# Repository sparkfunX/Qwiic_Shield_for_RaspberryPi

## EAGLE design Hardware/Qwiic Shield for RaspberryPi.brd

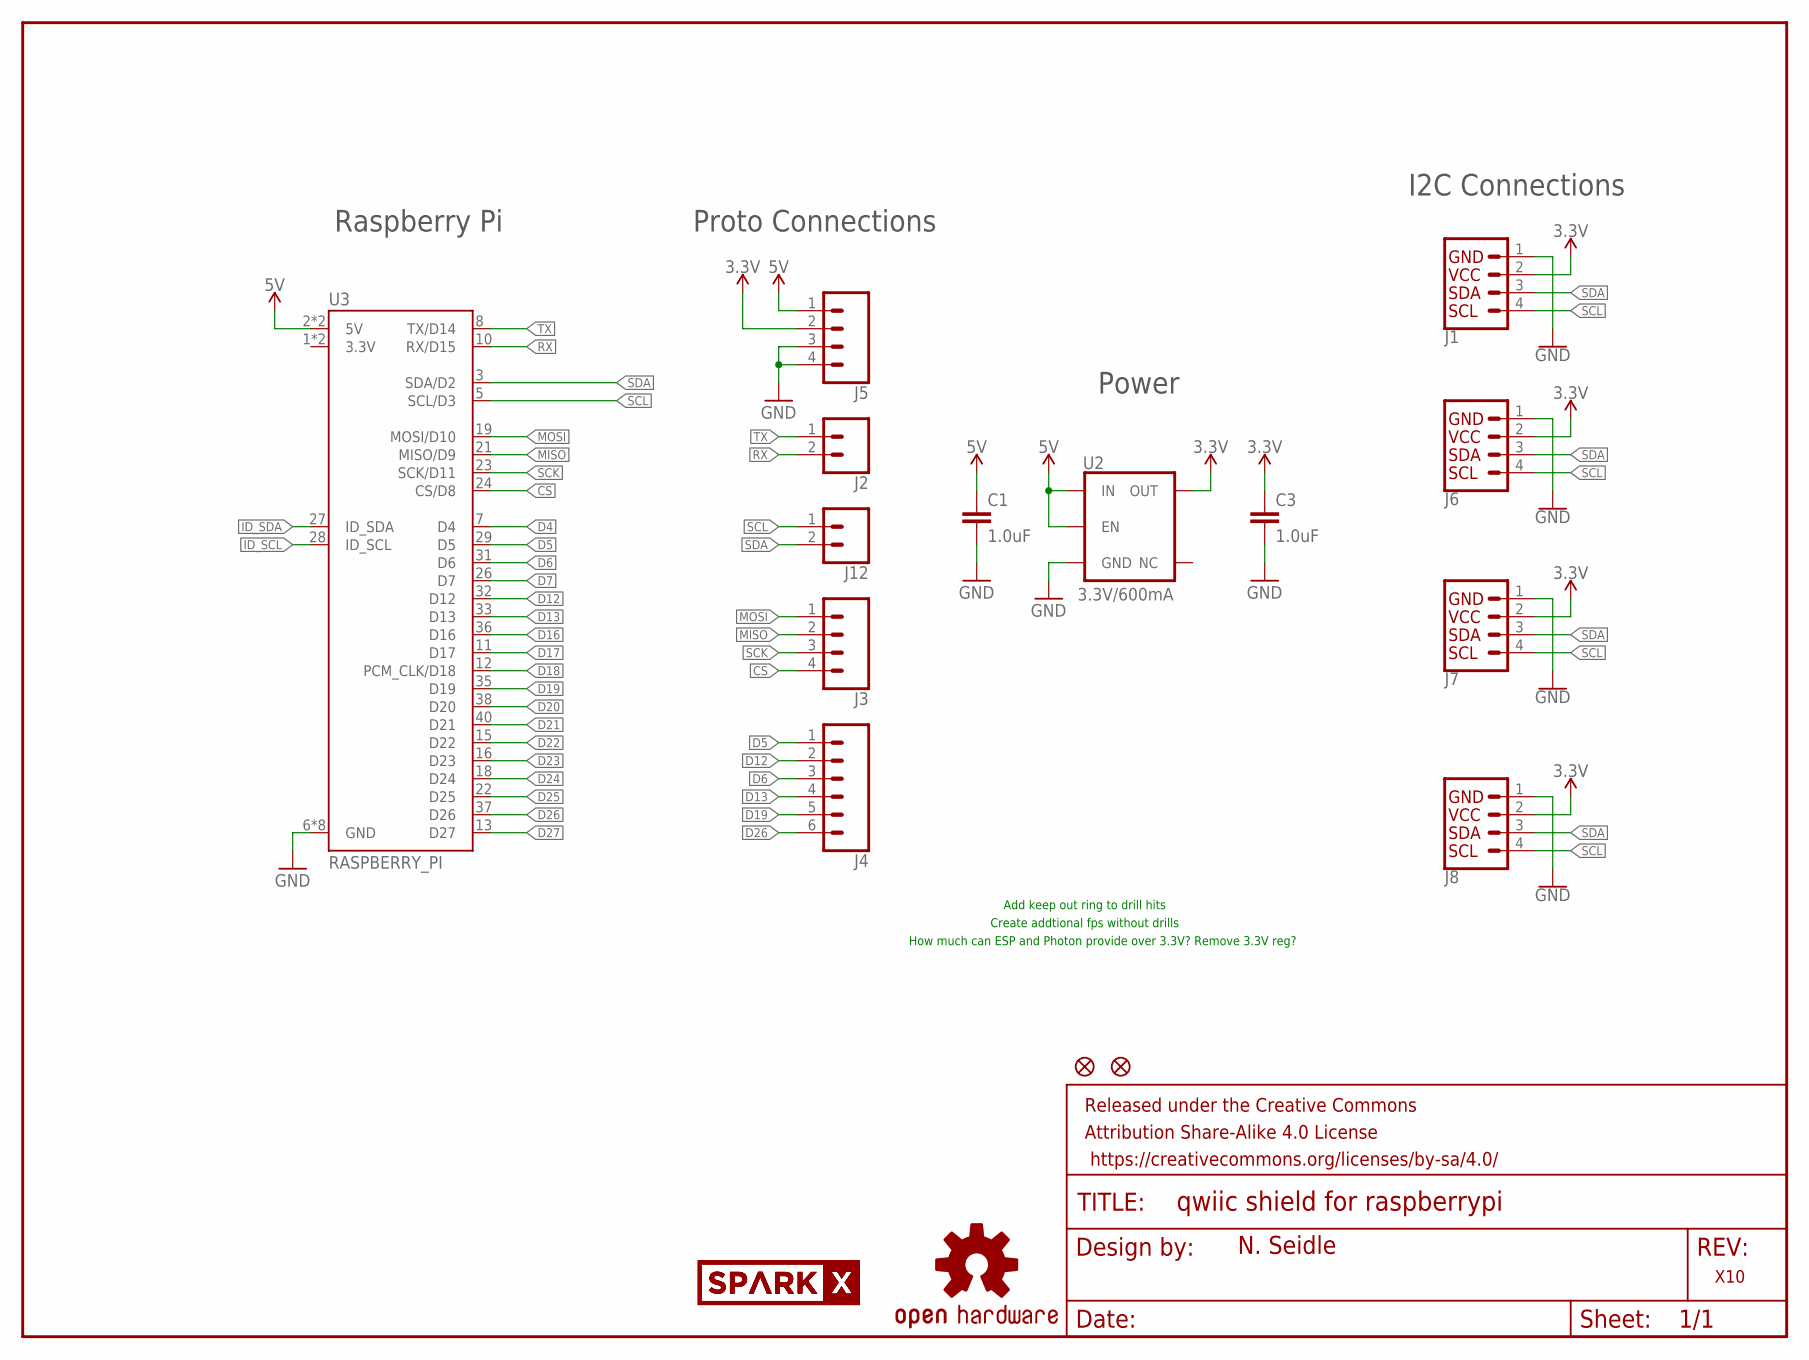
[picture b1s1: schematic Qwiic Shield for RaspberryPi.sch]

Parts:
C1, C3: 1.0uF; 0603
FD1, FD2: FIDUCIAL1X2; FIDUCIAL-1X2
FRAME1: FRAME-LETTER; CREATIVE_COMMONS
J1, J6, J7, J8: I2C_STANDARDJS-1MM; 1X04_1MM_RA
J2, J12: CONN_021X02_NO_SILK; 1X02_NO_SILK
J3, J5: CONN_041X04_NO_SILK; 1X04_NO_SILK
J4: CONN_06NO_SILK_FEMALE_PTH; 1X06_NO_SILK
LOGO1: OSHW-LOGOMINI; OSHW-LOGO-MINI
U2: 3.3V/600mA; SOT23-5
U3: RASPBERRY_PI; RASPBERRY_PI_SHIELD_HOLES
U$1: SPARKX-LOGO3; SPARKX-SMALL
U$2: SPARKX-LOGO5; SPARKX-LARGE

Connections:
3.3V: C3.1, J1.2 (VCC), J5.2, J6.2 (VCC), J7.2 (VCC), J8.2 (VCC), U2.5 (OUT)
5V: C1.1, J5.1, U2.1 (IN), U2.3 (EN), U3.2 (5V), U3.4 (5V)
CS: J3.4, U3.24 (CS/D8)
D4: U3.7 (D4)
D5: J4.1, U3.29 (D5)
D6: J4.3, U3.31 (D6)
D7: U3.26 (D7)
D12: J4.2, U3.32 (D12)
D13: J4.4, U3.33 (D13)
D16: U3.36 (D16)
D17: U3.11 (D17)
D18: U3.12 (PCM_CLK/D18)
D19: J4.5, U3.35 (D19)
D20: U3.38 (D20)
D21: U3.40 (D21)
D22: U3.15 (D22)
D23: U3.16 (D23)
D24: U3.18 (D24)
D25: U3.22 (D25)
D26: J4.6, U3.37 (D26)
D27: U3.13 (D27)
GND: C1.2, C3.2, J1.1 (GND), J5.3, J5.4, J6.1 (GND), J7.1 (GND), J8.1 (GND), U2.2 (GND), U3.6 (GND), U3.9 (GND), U3.14 (GND), U3.20 (GND), U3.25 (GND), U3.30 (GND), U3.34 (GND), U3.39 (GND)
ID_SCL: U3.28 (ID_SCL)
ID_SDA: U3.27 (ID_SDA)
MISO: J3.2, U3.21 (MISO/D9)
MOSI: J3.1, U3.19 (MOSI/D10)
RX: J2.2, U3.10 (RX/D15)
SCK: J3.3, U3.23 (SCK/D11)
SCL: J1.4 (SCL), J6.4 (SCL), J7.4 (SCL), J8.4 (SCL), J12.1, U3.5 (SCL/D3)
SDA: J1.3 (SDA), J6.3 (SDA), J7.3 (SDA), J8.3 (SDA), J12.2, U3.3 (SDA/D2)
TX: J2.1, U3.8 (TX/D14)

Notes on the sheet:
N. Seidle
Raspberry Pi
X10
I2C Connections
Proto Connections
Power
How much can ESP and Photon provide over 3.3V? Remove 3.3V reg?
Create addtional fps without drills
Add keep out ring to drill hits

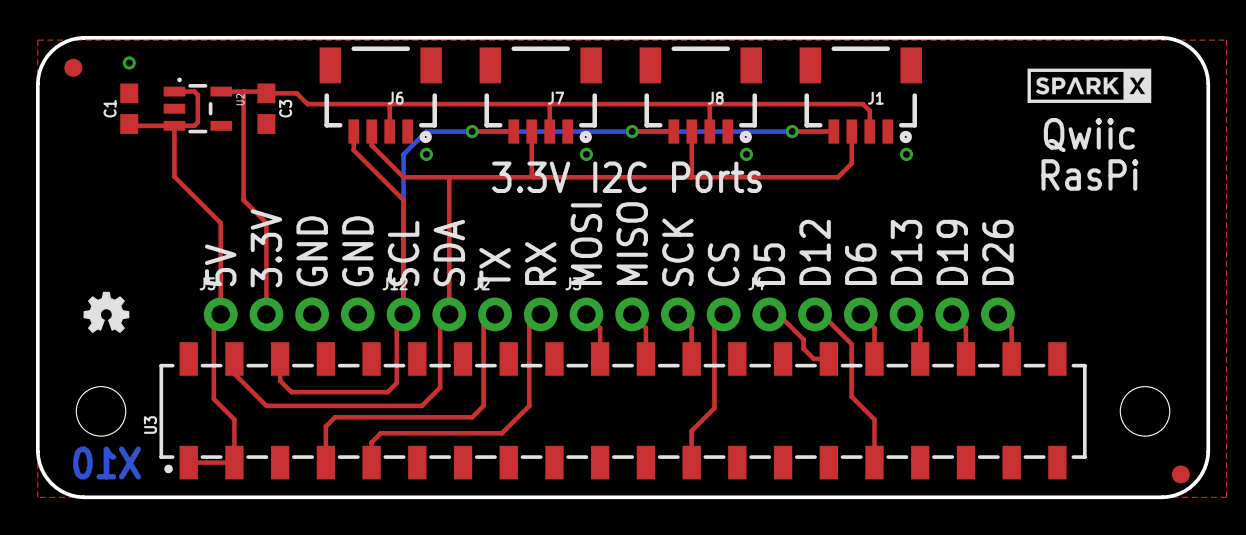
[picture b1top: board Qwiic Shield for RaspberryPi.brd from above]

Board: 2 copper layers, 65.0 x 25.5 mm, 19 parts (1 on the bottom side), 17 nets.

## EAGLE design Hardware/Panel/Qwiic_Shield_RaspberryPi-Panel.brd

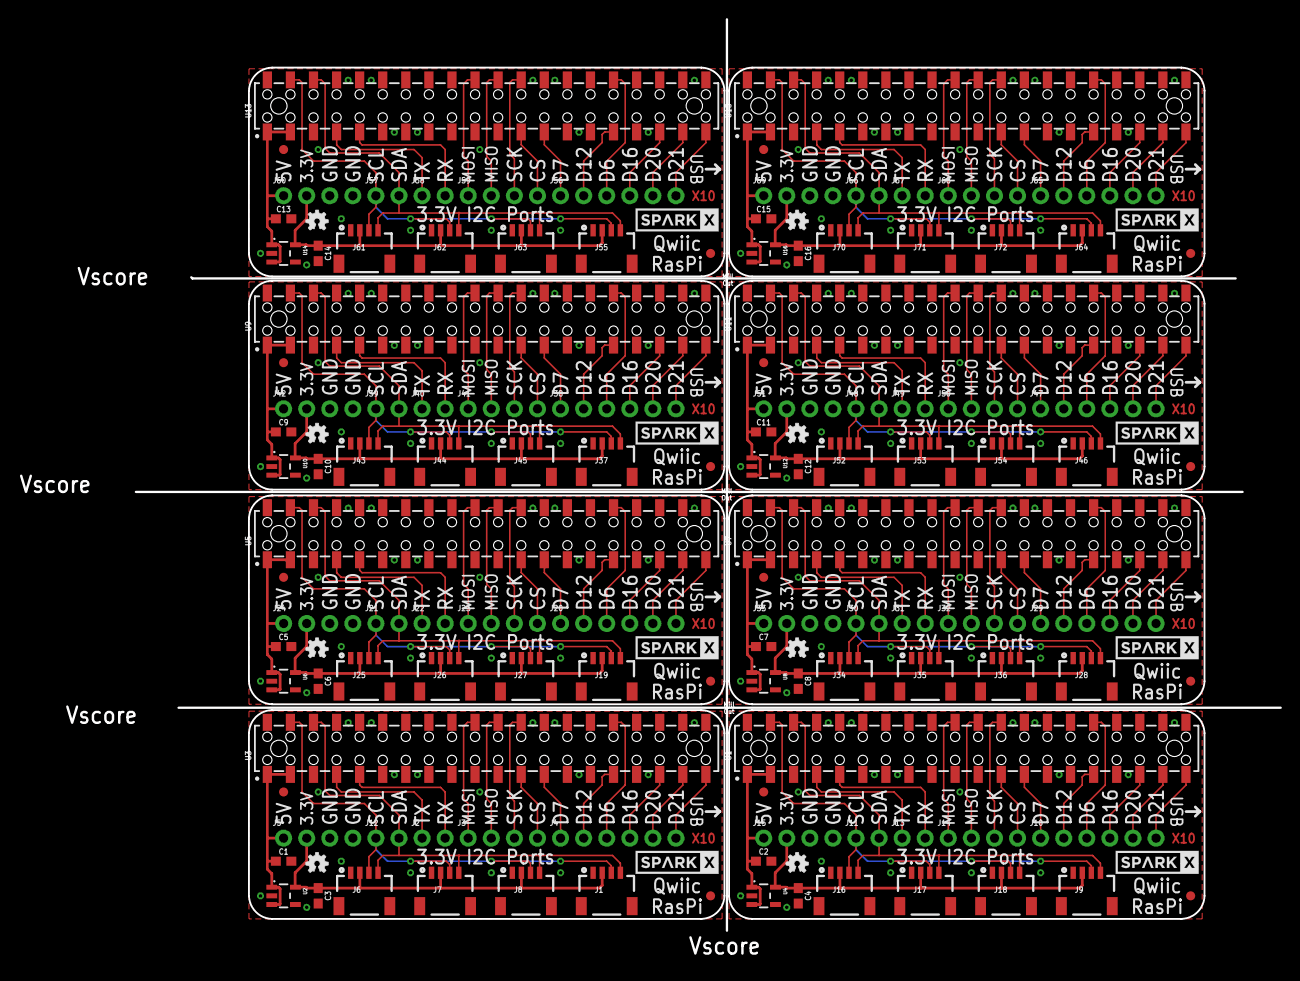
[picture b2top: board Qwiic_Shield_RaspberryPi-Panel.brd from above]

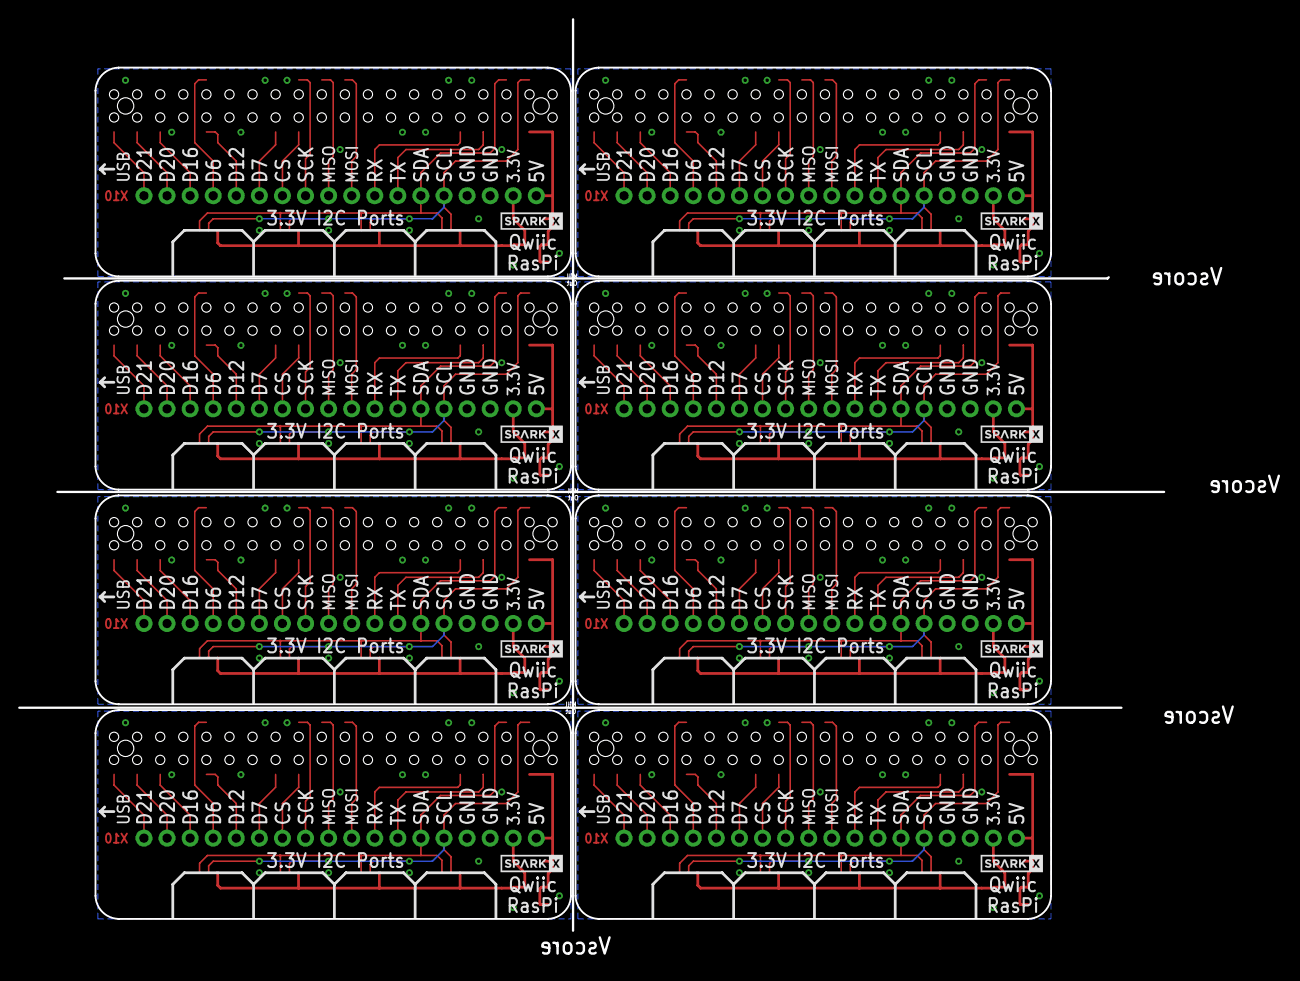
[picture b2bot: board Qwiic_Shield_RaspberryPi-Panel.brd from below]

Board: 2 copper layers, 138.8 x 103.8 mm, 144 parts (8 on the bottom side), 136 nets.

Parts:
C1, C2, C3, C4, C5, C6, C7, C8, C9, C10, C11, C12, C13, C14, C15, C16: 1.0uF; 0603
FD1, FD2, FD3, FD4, FD5, FD6, FD7, FD8, FD9, FD10, FD11, FD12, FD13, FD14, FD15, FD16: FIDUCIAL1X2; FIDUCIAL-1X2
J1, J6, J7, J8, J9, J16, J17, J18, J19, J25, J26, J27, J28, J34, J35, J36, J37, J43, J44, J45, J46, J52, J53, J54, J55, J61, J62, J63, J64, J70, J71, J72: 1X04_1MM_RA
J2, J11, J12, J13, J21, J22, J30, J31, J39, J40, J48, J49, J57, J58, J66, J67: 1X02_NO_SILK
J3, J5, J14, J15, J23, J24, J32, J33, J41, J42, J50, J51, J59, J60, J68, J69: 1X04_NO_SILK
J4, J10, J20, J29, J38, J47, J56, J65: 1X06_NO_SILK
LOGO1, LOGO2, LOGO3, LOGO4, LOGO5, LOGO6, LOGO7, LOGO8: OSHW-LOGOMINI; OSHW-LOGO-MINI
U1, U3, U5, U7, U9, U11, U13, U15: RASPBERRY_PI; RASPBERRY_PI_SHIELD_BOTTOM_ENTRY_NOHOLES
U2, U4, U6, U8, U10, U12, U14, U16: 3.3V/600mA; SOT23-5
U$1, U$3, U$5, U$7, U$9, U$11, U$13, U$15: SPARKX-LOGO3; SPARKX-SMALL
U$2, U$4, U$6, U$8, U$10, U$12, U$14, U$16: SPARKX-LOGO4; SPARKX-MEDIUM

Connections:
3.3V: C3.1, J1.2, J5.2, J6.2, J7.2, J8.2, U2.5
3.3V1: C4.1, J9.2, J15.2, J16.2, J17.2, J18.2, U4.5
3.3V2: C6.1, J19.2, J24.2, J25.2, J26.2, J27.2, U6.5
3.3V3: C8.1, J28.2, J33.2, J34.2, J35.2, J36.2, U8.5
3.3V4: C10.1, J37.2, J42.2, J43.2, J44.2, J45.2, U10.5
3.3V5: C12.1, J46.2, J51.2, J52.2, J53.2, J54.2, U12.5
3.3V6: C14.1, J55.2, J60.2, J61.2, J62.2, J63.2, U14.5
3.3V7: C16.1, J64.2, J69.2, J70.2, J71.2, J72.2, U16.5
5V: C1.1, J5.1, U2.1, U2.3, U3.2, U3.4
5V1: C2.1, J15.1, U1.2, U1.4, U4.1, U4.3
5V2: C5.1, J24.1, U5.2, U5.4, U6.1, U6.3
5V3: C7.1, J33.1, U7.2, U7.4, U8.1, U8.3
5V4: C9.1, J42.1, U9.2, U9.4, U10.1, U10.3
5V5: C11.1, J51.1, U11.2, U11.4, U12.1, U12.3
5V6: C13.1, J60.1, U13.2, U13.4, U14.1, U14.3
5V7: C15.1, J69.1, U15.2, U15.4, U16.1, U16.3
CS: J3.4, U3.24
CS1: J14.4, U1.24
CS2: J23.4, U5.24
CS3: J32.4, U7.24
CS4: J41.4, U9.24
CS5: J50.4, U11.24
CS6: J59.4, U13.24
CS7: J68.4, U15.24
D2: J10.3, U1.31
D3: J10.1, U1.26
D6: J4.3, U3.31
D7: J4.1, U3.26
D8: J10.2, U1.32
D10: J10.4, U1.36
D12: J4.2, U3.32
D16: J4.4, U3.36
D20: J4.5, U3.38
D21: J4.6, U3.40
D28: J10.5, U1.38
D29: J10.6, U1.40
D38: J20.3, U5.31
D39: J20.1, U5.26
D40: J20.2, U5.32
D42: J20.4, U5.36
D46: J20.5, U5.38
D47: J20.6, U5.40
D56: J29.3, U7.31
D57: J29.1, U7.26
D58: J29.2, U7.32
D60: J29.4, U7.36
D64: J29.5, U7.38
D65: J29.6, U7.40
D74: J38.3, U9.31
D75: J38.1, U9.26
D76: J38.2, U9.32
D78: J38.4, U9.36
D82: J38.5, U9.38
D83: J38.6, U9.40
D92: J47.3, U11.31
D93: J47.1, U11.26
D94: J47.2, U11.32
D96: J47.4, U11.36
D100: J47.5, U11.38
D101: J47.6, U11.40
D110: J56.3, U13.31
D111: J56.1, U13.26
D112: J56.2, U13.32
D114: J56.4, U13.36
D118: J56.5, U13.38
D119: J56.6, U13.40
D128: J65.3, U15.31
D129: J65.1, U15.26
D130: J65.2, U15.32
D132: J65.4, U15.36
D136: J65.5, U15.38
D137: J65.6, U15.40
GND: C1.2, C3.2, J1.1, J5.3, J5.4, J6.1, J7.1, J8.1, U2.2, U3.6, U3.9, U3.14, U3.20, U3.25, U3.30, U3.34, U3.39
GND1: C2.2, C4.2, J9.1, J15.3, J15.4, J16.1, J17.1, J18.1, U1.6, U1.9, U1.14, U1.20, U1.25, U1.30, U1.34, U1.39, U4.2
GND2: C5.2, C6.2, J19.1, J24.3, J24.4, J25.1, J26.1, J27.1, U5.6, U5.9, U5.14, U5.20, U5.25, U5.30, U5.34, U5.39, U6.2
GND3: C7.2, C8.2, J28.1, J33.3, J33.4, J34.1, J35.1, J36.1, U7.6, U7.9, U7.14, U7.20, U7.25, U7.30, U7.34, U7.39, U8.2
GND4: C9.2, C10.2, J37.1, J42.3, J42.4, J43.1, J44.1, J45.1, U9.6, U9.9, U9.14, U9.20, U9.25, U9.30, U9.34, U9.39, U10.2
GND5: C11.2, C12.2, J46.1, J51.3, J51.4, J52.1, J53.1, J54.1, U11.6, U11.9, U11.14, U11.20, U11.25, U11.30, U11.34, U11.39, U12.2
GND6: C13.2, C14.2, J55.1, J60.3, J60.4, J61.1, J62.1, J63.1, U13.6, U13.9, U13.14, U13.20, U13.25, U13.30, U13.34, U13.39, U14.2
GND7: C15.2, C16.2, J64.1, J69.3, J69.4, J70.1, J71.1, J72.1, U15.6, U15.9, U15.14, U15.20, U15.25, U15.30, U15.34, U15.39, U16.2
MISO: J3.2, U3.21
MISO1: J14.2, U1.21
MISO2: J23.2, U5.21
MISO3: J32.2, U7.21
MISO4: J41.2, U9.21
MISO5: J50.2, U11.21
MISO6: J59.2, U13.21
MISO7: J68.2, U15.21
MOSI: J3.1, U3.19
MOSI1: J14.1, U1.19
MOSI2: J23.1, U5.19
MOSI3: J32.1, U7.19
MOSI4: J41.1, U9.19
MOSI5: J50.1, U11.19
MOSI6: J59.1, U13.19
MOSI7: J68.1, U15.19
RX: J2.2, U3.10
RX1: J13.2, U1.10
RX2: J22.2, U5.10
RX3: J31.2, U7.10
RX4: J40.2, U9.10
RX5: J49.2, U11.10
RX6: J58.2, U13.10
RX7: J67.2, U15.10
SCK: J3.3, U3.23
SCK1: J14.3, U1.23
SCK2: J23.3, U5.23
SCK3: J32.3, U7.23
SCK4: J41.3, U9.23
SCK5: J50.3, U11.23
SCK6: J59.3, U13.23
SCK7: J68.3, U15.23
SCL: J1.4, J6.4, J7.4, J8.4, J12.2, U3.5
SCL1: J9.4, J11.2, J16.4, J17.4, J18.4, U1.5
SCL2: J19.4, J21.2, J25.4, J26.4, J27.4, U5.5
SCL3: J28.4, J30.2, J34.4, J35.4, J36.4, U7.5
SCL4: J37.4, J39.2, J43.4, J44.4, J45.4, U9.5
SCL5: J46.4, J48.2, J52.4, J53.4, J54.4, U11.5
SCL6: J55.4, J57.2, J61.4, J62.4, J63.4, U13.5
SCL7: J64.4, J66.2, J70.4, J71.4, J72.4, U15.5
SDA: J1.3, J6.3, J7.3, J8.3, J12.1, U3.3
SDA1: J9.3, J11.1, J16.3, J17.3, J18.3, U1.3
SDA2: J19.3, J21.1, J25.3, J26.3, J27.3, U5.3
SDA3: J28.3, J30.1, J34.3, J35.3, J36.3, U7.3
SDA4: J37.3, J39.1, J43.3, J44.3, J45.3, U9.3
SDA5: J46.3, J48.1, J52.3, J53.3, J54.3, U11.3
SDA6: J55.3, J57.1, J61.3, J62.3, J63.3, U13.3
SDA7: J64.3, J66.1, J70.3, J71.3, J72.3, U15.3
TX: J2.1, U3.8
TX1: J13.1, U1.8
TX2: J22.1, U5.8
TX3: J31.1, U7.8
TX4: J40.1, U9.8
TX5: J49.1, U11.8
TX6: J58.1, U13.8
TX7: J67.1, U15.8

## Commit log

2017-04-09 :confetti_ball: Added .gitattributes & .gitignore files
2017-04-17 Adding panel files
2017-05-22 Adding readme
2017-08-30 New panel with fixed soldermask aperatures removed from vias.

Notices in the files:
parts and their libraries:
SparkFun-Aesthetics: Licensing: CC v3.0 Share-Alike You are welcome to use this library for commercial purposes.
SparkFun-Connectors: Licensing: Creative Commons ShareAlike 4.0 International - https://creativecommons.org/licenses/by-sa/4.0
SparkFun-Aesthetics: Released under the Creative Commons
